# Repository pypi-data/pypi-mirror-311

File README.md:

# PyPI code 311

This repository is part of a project to make all code in PyPI as accessible as possible. For more information 
on the project and to find out how to utilise this data, see the website: https://py-code.org/

This repo contains 50000 packages uploaded to PyPI between 
2024-11-25 23:24 and 2024-11-29 07:17.

The repo is 99% (49999/50000) complete.

Package contents can be found [in the code branch](https://github.com/pypi-data/pypi-mirror-311/tree/code/packages).

A browsable package list for all repositories [all packages here](https://py-code.org/repositories/pypi-mirror-311).

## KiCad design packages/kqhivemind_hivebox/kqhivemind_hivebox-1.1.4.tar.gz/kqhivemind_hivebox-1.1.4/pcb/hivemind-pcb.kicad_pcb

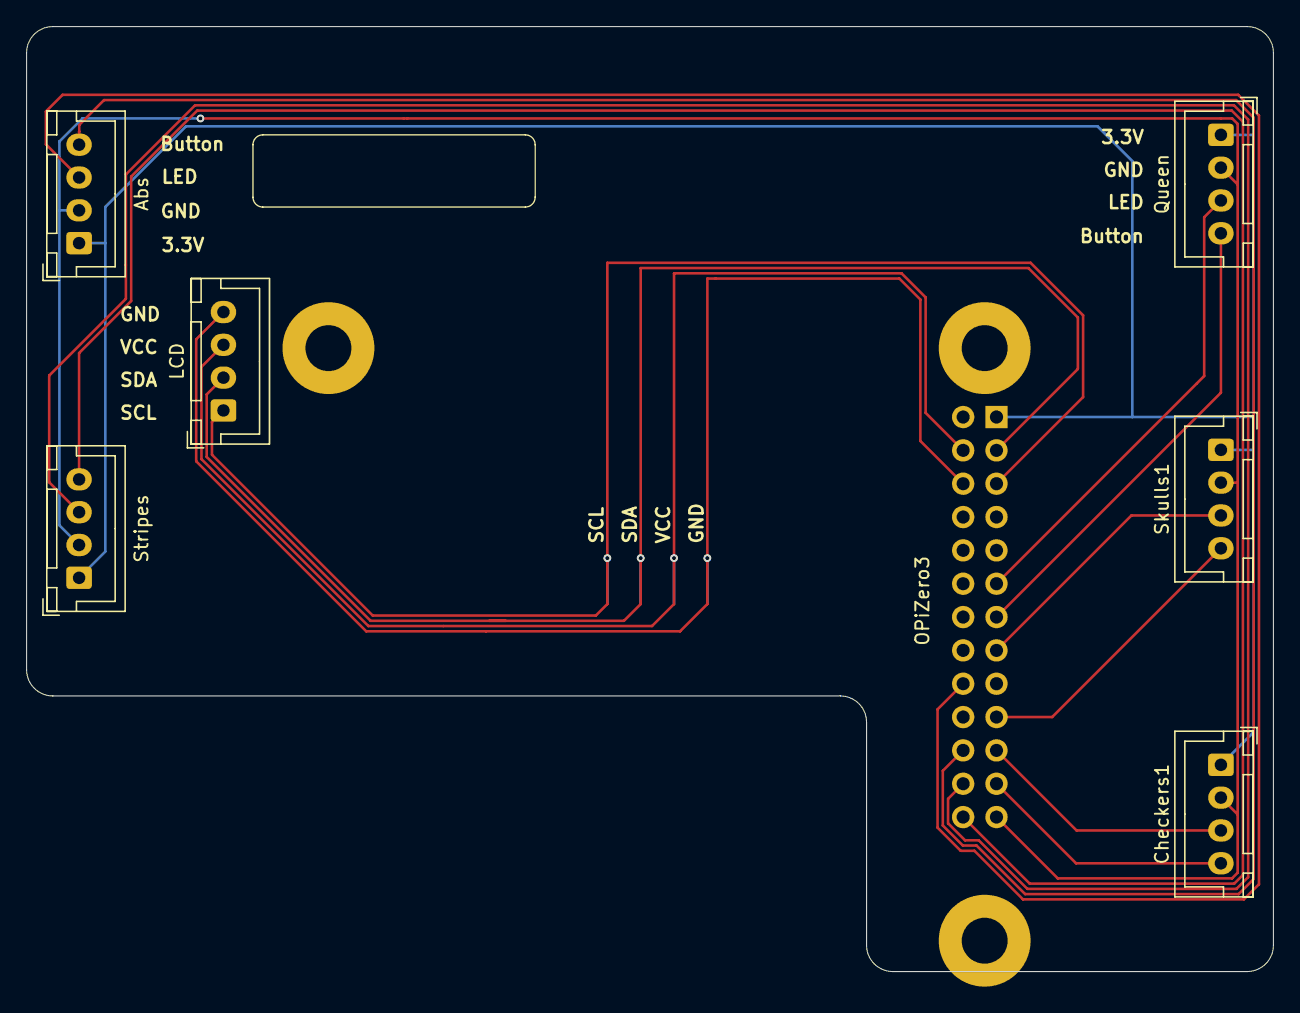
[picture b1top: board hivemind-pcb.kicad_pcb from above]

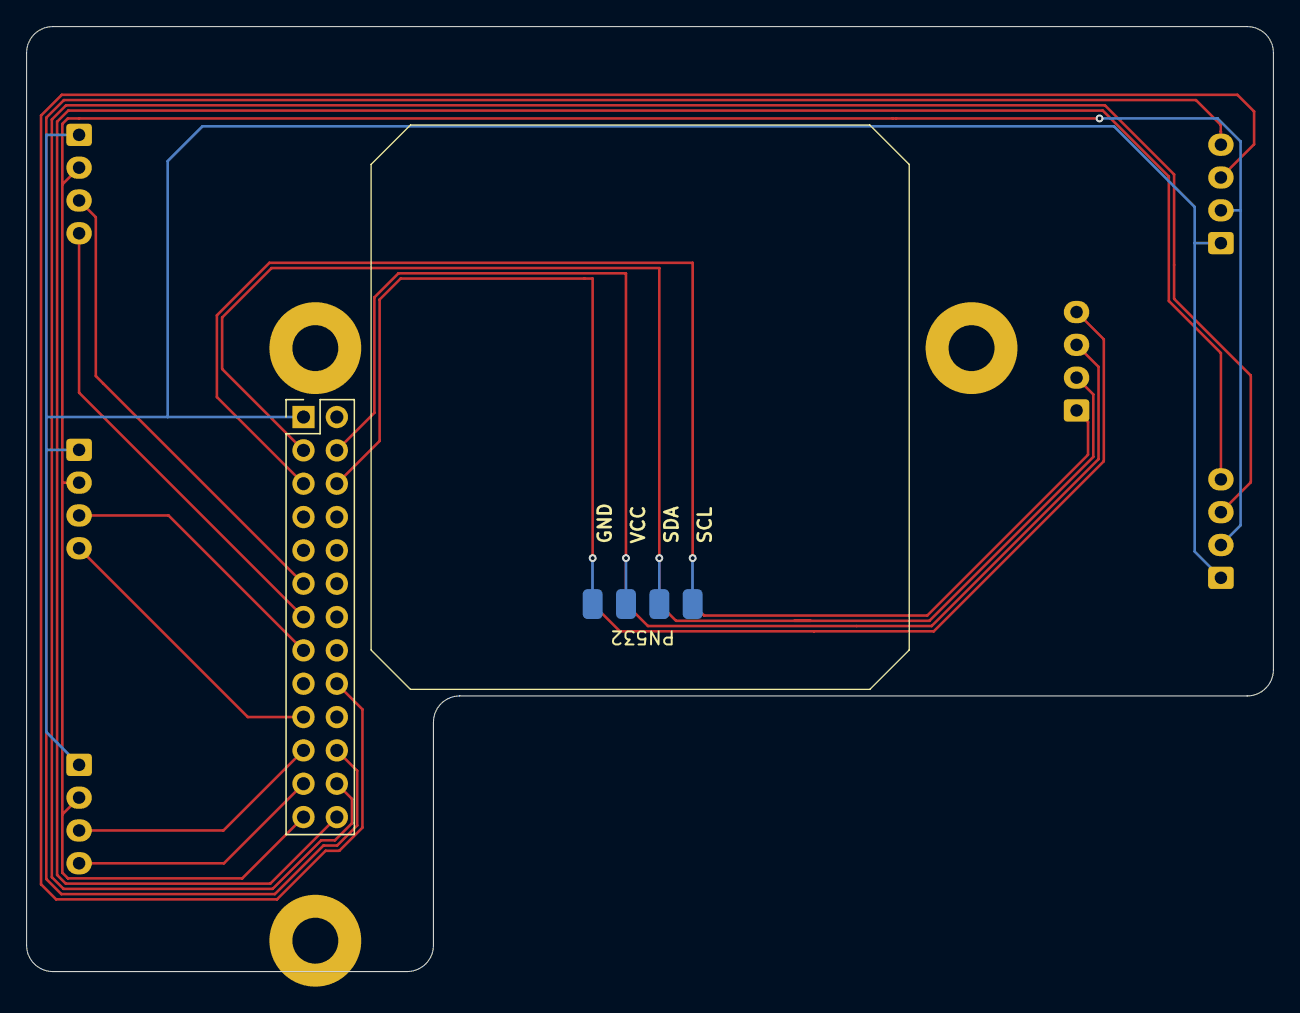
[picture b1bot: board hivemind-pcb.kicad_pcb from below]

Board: 2 copper layers, 95.0 x 72.0 mm, 8 parts (2 on the bottom side), 12 nets.

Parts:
Abs: Conn_01x04_Pin; JST_XH_B4B-XH-A_1x04_P2.50mm_Vertical
Checkers1: Conn_01x04_Pin; JST_XH_B4B-XH-A_1x04_P2.50mm_Vertical
LCD: Conn_01x04_Pin; JST_XH_B4B-XH-A_1x04_P2.50mm_Vertical
OPiZero3: Conn_02x13_Odd_Even; PinHeader_2x13_P2.54mm_Vertical
PN532: Conn_01x04_Pin; Solder Pads 01x04 2.54mm
Queen: Conn_01x04_Pin; JST_XH_B4B-XH-A_1x04_P2.50mm_Vertical
Skulls1: Conn_01x04_Pin; JST_XH_B4B-XH-A_1x04_P2.50mm_Vertical
Stripes: Conn_01x04_Pin; JST_XH_B4B-XH-A_1x04_P2.50mm_Vertical

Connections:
unnamed: Checkers1.1, OPiZero3.1 (3.3V), Queen.1, Skulls1.1, Stripes.1
unnamed: Checkers1.2, OPiZero3.25, Queen.2, Skulls1.2, Stripes.2
unnamed: LCD.4 (GND), OPiZero3.6, PN532.4 (GND)
unnamed: LCD.1 (SCK), OPiZero3.5 (SCK), PN532.1 (SCK)
unnamed: LCD.2 (SDA), OPiZero3.3 (SDA), PN532.2 (SDA)
unnamed: LCD.3 (VCC), OPiZero3.4, PN532.3 (VCC)
unnamed: OPiZero3.13 (PC5), Queen.4
unnamed: OPiZero3.11 (PC6), Queen.3
unnamed: OPiZero3.15 (PC8), Skulls1.3
unnamed: OPiZero3.19, Skulls1.4
unnamed: OPiZero3.24, Stripes.3
unnamed: OPiZero3.26, Stripes.4

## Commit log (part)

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2024-12-07 Add package xgcondb/743.641.349/xgcondb-743.641.349-cp310-cp310-win_amd64.whl
2024-12-07 Add package fake-bge-module/20241129/fake_bge_module-20241129-py3-none-any.whl
2024-12-07 Add package bsg-ide/2.0.1/bsg_ide-2.0.1-py3-none-any.whl
2024-12-07 Add package xgcondb/2832.76.37/xgcondb-2832.76.37-cp310-cp310-win_amd64.whl
2024-12-07 Add package xgcondb/734.164.978/xgcondb-734.164.978-cp37-cp37m-manylinux2014_x86_64.manylinux_2_17_x86_64.whl
2024-12-07 Add package xgcondb/2833.70.52/xgcondb-2833.70.52-cp37-cp37m-win_amd64.whl
2024-12-07 Add package xgcondb/5983.907.328/xgcondb-5983.907.328-cp311-cp311-win_amd64.whl
2024-12-07 Add package xgcondb/2843.58.11/xgcondb-2843.58.11-cp39-cp39-manylinux2014_aarch64.manylinux_2_17_aarch64.whl
2024-12-07 Add package xgcondb/734.414.150/xgcondb-734.414.150-cp37-cp37m-win_amd64.whl
2024-12-07 Add package xgcondb/2838.67.75/xgcondb-2838.67.75-cp39-cp39-manylinux2014_aarch64.manylinux_2_17_aarch64.whl
2024-12-07 Add package xgcondb/2833.70.52/xgcondb-2833.70.52-cp39-cp39-win_amd64.whl
2024-12-07 Add package xgcondb/5973.661.293/xgcondb-5973.661.293-cp310-cp310-win_amd64.whl
2024-12-07 Add package seatools/1.0.13/seatools-1.0.13-py3-none-any.whl
2024-12-07 Add package xgcondb/725.204.402/xgcondb-725.204.402-cp310-cp310-manylinux2014_x86_64.manylinux_2_17_x86_64.whl
2024-12-07 Add package streamlit-nightly/1.40.3.dev20241128/streamlit_nightly-1.40.3.dev20241128.tar.gz
2024-12-07 Add package xgcondb/5991.19.593/xgcondb-5991.19.593-cp37-cp37m-manylinux2014_x86_64.manylinux_2_17_x86_64.whl
2024-12-07 Add package xgcondb/5983.53.251/xgcondb-5983.53.251-cp37-cp37m-win_amd64.whl
2024-12-07 Add package xgcondb/2853.74.16/xgcondb-2853.74.16-cp39-cp39-manylinux2014_aarch64.manylinux_2_17_aarch64.whl
2024-12-07 Add package xgcondb/2853.66.40/xgcondb-2853.66.40-cp38-cp38-manylinux2014_x86_64.manylinux_2_17_x86_64.whl
2024-12-07 Add package xgcondb/735.844.684/xgcondb-735.844.684-cp311-cp311-win_amd64.whl
2024-12-07 Add package xgcondb/5992.370.685/xgcondb-5992.370.685-cp39-cp39-win_amd64.whl
2024-12-07 Add package xgcondb/5984.336.412/xgcondb-5984.336.412-cp311-cp311-win_amd64.whl
2024-12-07 Add package xgcondb/6008.274.512/xgcondb-6008.274.512-cp37-cp37m-win_amd64.whl
2024-12-07 Add package xgcondb/731.9.980/xgcondb-731.9.980-cp310-cp310-manylinux2014_x86_64.manylinux_2_17_x86_64.whl
2024-12-07 Add package xgcondb/725.7.854/xgcondb-725.7.854-cp310-cp310-manylinux2014_x86_64.manylinux_2_17_x86_64.whl
2024-12-07 Add package xgcondb/726.249.769/xgcondb-726.249.769-cp311-cp311-manylinux2014_x86_64.manylinux_2_17_x86_64.whl
2024-12-07 Add package xgcondb/2839.36.70/xgcondb-2839.36.70-cp38-cp38-manylinux2014_aarch64.manylinux_2_17_aarch64.whl
2024-12-07 Add package xgcondb/744.346.258/xgcondb-744.346.258-cp38-cp38-win_amd64.whl
2024-12-07 Add package xgcondb/5986.182.943/xgcondb-5986.182.943-cp38-cp38-win_amd64.whl
2024-12-07 Add package xgcondb/6009.5.900/xgcondb-6009.5.900-cp38-cp38-manylinux2014_x86_64.manylinux_2_17_x86_64.whl
2024-12-07 Add package xgcondb/2863.58.40/xgcondb-2863.58.40-cp37-cp37m-manylinux2014_aarch64.manylinux_2_17_aarch64.whl
2024-12-07 Add package xgcondb/2840.84.41/xgcondb-2840.84.41-cp38-cp38-manylinux2014_aarch64.manylinux_2_17_aarch64.whl
2024-12-07 Add package xgcondb/736.840.889/xgcondb-736.840.889-cp37-cp37m-win_amd64.whl
2024-12-07 Add package xgcondb/2855.65.91/xgcondb-2855.65.91-cp37-cp37m-manylinux2014_aarch64.manylinux_2_17_aarch64.whl
2024-12-07 Add package aliyun-python-sdk-bpstudio/1.0.13/aliyun_python_sdk_bpstudio-1.0.13-py2.py3-none-any.whl
2024-12-07 Add package xgcondb/751.653.359/xgcondb-751.653.359-cp37-cp37m-manylinux2014_aarch64.manylinux_2_17_aarch64.whl
2024-12-07 Add package xgcondb/5993.344.625/xgcondb-5993.344.625-cp39-cp39-win_amd64.whl
2024-12-07 Add package xgcondb/6008.204.105/xgcondb-6008.204.105-cp39-cp39-win_amd64.whl
2024-12-07 Add package xgcondb/740.701.827/xgcondb-740.701.827-cp39-cp39-manylinux2014_x86_64.manylinux_2_17_x86_64.whl
2024-12-07 Add package smart-steganography-lib/0.1.1/smart_steganography_lib-0.1.1-py3-none-any.whl
2024-12-07 Add package xgcondb/745.171.814/xgcondb-745.171.814-cp37-cp37m-manylinux2014_aarch64.manylinux_2_17_aarch64.whl
2024-12-07 Add package synth-sdk/0.2.80/synth_sdk-0.2.80-py3-none-any.whl
2024-12-07 Add package xgcondb/752.395.285/xgcondb-752.395.285-cp39-cp39-manylinux2014_aarch64.manylinux_2_17_aarch64.whl
2024-12-07 Add package EwanSonicConnector/0.1.7/ewansonicconnector-0.1.7.tar.gz
2024-12-07 Add package xgcondb/6010.245.110/xgcondb-6010.245.110-cp39-cp39-manylinux2014_aarch64.manylinux_2_17_aarch64.whl
2024-12-07 Add package xgcondb/2846.0.64/xgcondb-2846.0.64-cp39-cp39-win_amd64.whl
2024-12-07 Add package xgcondb/6010.481.789/xgcondb-6010.481.789-cp38-cp38-manylinux2014_aarch64.manylinux_2_17_aarch64.whl
2024-12-07 Add package mg-pso-gui/0.2.14/mg_pso_gui-0.2.14-py3-none-any.whl
2024-12-07 Add package xgcondb/5997.414.393/xgcondb-5997.414.393-cp37-cp37m-manylinux2014_x86_64.manylinux_2_17_x86_64.whl
2024-12-07 Add package ailia-llm/1.2.1.0/ailia_llm-1.2.1.0-py3-none-any.whl
2024-12-07 Add package xgcondb/5996.815.127/xgcondb-5996.815.127-cp39-cp39-manylinux2014_x86_64.manylinux_2_17_x86_64.whl
2024-12-07 Add package django-swifty/0.0.44/django_swifty-0.0.44.tar.gz
2024-12-07 Add package xgcondb/6000.465.492/xgcondb-6000.465.492-cp39-cp39-win_amd64.whl
2024-12-07 Add package xgcondb/753.969.148/xgcondb-753.969.148-cp37-cp37m-win_amd64.whl
2024-12-07 Add package xgcondb/737.258.167/xgcondb-737.258.167-cp37-cp37m-win_amd64.whl
2024-12-07 Add package xgcondb/6001.226.428/xgcondb-6001.226.428-cp310-cp310-manylinux2014_x86_64.manylinux_2_17_x86_64.whl
2024-12-07 Add package aiotica/1.0.12/aiotica-1.0.12-py3-none-any.whl
2024-12-07 Add package nemo-library/1.1.18/nemo_library-1.1.18.tar.gz
2024-12-07 Add package xgcondb/2847.62.7/xgcondb-2847.62.7-cp39-cp39-manylinux2014_x86_64.manylinux_2_17_x86_64.whl
2024-12-07 Add package rjj/0.8.9/rjj-0.8.9.tar.gz
2024-12-07 Add package xgcondb/746.75.683/xgcondb-746.75.683-cp39-cp39-manylinux2014_aarch64.manylinux_2_17_aarch64.whl
2024-12-07 Add package xgcondb/2865.72.17/xgcondb-2865.72.17-cp310-cp310-manylinux2014_x86_64.manylinux_2_17_x86_64.whl
2024-12-07 Add package xgcondb/740.246.716/xgcondb-740.246.716-cp37-cp37m-manylinux2014_x86_64.manylinux_2_17_x86_64.whl
2024-12-07 Add package xgcondb/6002.656.897/xgcondb-6002.656.897-cp310-cp310-win_amd64.whl
2024-12-07 Add package xgcondb/6026.1000.76/xgcondb-6026.1000.76-cp311-cp311-manylinux2014_x86_64.manylinux_2_17_x86_64.whl
2024-12-07 Add package aiotica/1.0.12/aiotica-1.0.12.tar.gz
2024-12-07 Add package xgcondb/754.523.504/xgcondb-754.523.504-cp37-cp37m-win_amd64.whl
2024-12-07 Add package xgcondb/6011.55.670/xgcondb-6011.55.670-cp311-cp311-manylinux2014_x86_64.manylinux_2_17_x86_64.whl
2024-12-07 Add package zope.app.wsgi/5.3/zope.app.wsgi-5.3-py3-none-any.whl
2024-12-07 Add package xgcondb/6012.36.609/xgcondb-6012.36.609-cp311-cp311-win_amd64.whl
2024-12-07 Add package xgcondb/2857.78.22/xgcondb-2857.78.22-cp39-cp39-manylinux2014_aarch64.manylinux_2_17_aarch64.whl
2024-12-07 Add package xgcondb/2866.96.13/xgcondb-2866.96.13-cp38-cp38-manylinux2014_x86_64.manylinux_2_17_x86_64.whl
2024-12-07 Add package xgcondb/739.371.181/xgcondb-739.371.181-cp310-cp310-win_amd64.whl
2024-12-07 Add package xgcondb/2866.74.29/xgcondb-2866.74.29-cp310-cp310-win_amd64.whl
2024-12-07 Add package xgcondb/755.456.312/xgcondb-755.456.312-cp39-cp39-manylinux2014_x86_64.manylinux_2_17_x86_64.whl
2024-12-07 Add package xursparks/1.1.2/xursparks-1.1.2-py3-none-any.whl
2024-12-07 Add package youqu-playbook/2024.11.29/youqu_playbook-2024.11.29-py3-none-any.whl
2024-12-07 Add package xgcondb/755.392.570/xgcondb-755.392.570-cp39-cp39-manylinux2014_x86_64.manylinux_2_17_x86_64.whl
2024-12-07 Add package xgcondb/6029.716.152/xgcondb-6029.716.152-cp37-cp37m-win_amd64.whl
2024-12-07 Add package xgcondb/742.103.16/xgcondb-742.103.16-cp311-cp311-manylinux2014_x86_64.manylinux_2_17_x86_64.whl
2024-12-07 Add package xgcondb/750.948.318/xgcondb-750.948.318-cp311-cp311-win_amd64.whl
2024-12-07 Add package xgcondb/749.107.109/xgcondb-749.107.109-cp37-cp37m-manylinux2014_aarch64.manylinux_2_17_aarch64.whl
2024-12-07 Add package xgcondb/2851.82.83/xgcondb-2851.82.83-cp310-cp310-manylinux2014_x86_64.manylinux_2_17_x86_64.whl
2024-12-07 Add package xgcondb/2868.53.12/xgcondb-2868.53.12-cp38-cp38-manylinux2014_aarch64.manylinux_2_17_aarch64.whl
2024-12-07 Add package xgcondb/756.160.564/xgcondb-756.160.564-cp39-cp39-manylinux2014_aarch64.manylinux_2_17_aarch64.whl
2024-12-07 Add package xgcondb/6029.631.377/xgcondb-6029.631.377-cp38-cp38-manylinux2014_x86_64.manylinux_2_17_x86_64.whl
2024-12-07 Add package InvoiceBuddy/0.3.1/invoicebuddy-0.3.1-py3-none-any.whl
2024-12-07 Add package mcsp/1.1.2/mcsp-1.1.2-py3-none-any.whl
2024-12-07 Add package remics/0.1.1/remics-0.1.1-py2.py3-none-any.whl
2024-12-07 Add package xgcondb/2858.58.67/xgcondb-2858.58.67-cp39-cp39-win_amd64.whl
2024-12-07 Add package xgcondb/751.331.865/xgcondb-751.331.865-cp37-cp37m-win_amd64.whl
2024-12-07 Add package xgcondb/2869.46.36/xgcondb-2869.46.36-cp39-cp39-manylinux2014_aarch64.manylinux_2_17_aarch64.whl
2024-12-07 Add package xgcondb/756.998.863/xgcondb-756.998.863-cp38-cp38-manylinux2014_x86_64.manylinux_2_17_x86_64.whl
2024-12-07 Add package xgcondb/749.650.587/xgcondb-749.650.587-cp311-cp311-manylinux2014_x86_64.manylinux_2_17_x86_64.whl
2024-12-07 Add package autonomize-sdk-python/0.0.0/autonomize_sdk_python-0.0.0-py3-none-any.whl
2024-12-07 Add package xgcondb/6018.471.398/xgcondb-6018.471.398-cp38-cp38-win_amd64.whl
2024-12-07 Add package xgcondb/6031.574.585/xgcondb-6031.574.585-cp39-cp39-manylinux2014_aarch64.manylinux_2_17_aarch64.whl
2024-12-07 Add package xgcondb/2858.85.71/xgcondb-2858.85.71-cp38-cp38-manylinux2014_x86_64.manylinux_2_17_x86_64.whl
2024-12-07 Add package xgcondb/748.97.298/xgcondb-748.97.298-cp38-cp38-manylinux2014_x86_64.manylinux_2_17_x86_64.whl
2024-12-07 Add package xgcondb/748.97.298/xgcondb-748.97.298-cp310-cp310-manylinux2014_x86_64.manylinux_2_17_x86_64.whl
2024-12-07 Add package alibabacloud-bpstudio20210931/6.0.3/alibabacloud_bpstudio20210931-6.0.3-py3-none-any.whl
2024-12-07 Add package xgcondb/2870.33.95/xgcondb-2870.33.95-cp38-cp38-manylinux2014_aarch64.manylinux_2_17_aarch64.whl
2024-12-07 Add package xgcondb/6016.407.462/xgcondb-6016.407.462-cp38-cp38-win_amd64.whl
2024-12-07 Add package xgcondb/6033.747.316/xgcondb-6033.747.316-cp310-cp310-win_amd64.whl
2024-12-07 Add package bsg-ide/2.2/bsg_ide-2.2-py3-none-any.whl
2024-12-07 Add package xgcondb/2871.29.55/xgcondb-2871.29.55-cp37-cp37m-manylinux2014_x86_64.manylinux_2_17_x86_64.whl
2024-12-07 Add package xgcondb/6038.460.532/xgcondb-6038.460.532-cp37-cp37m-win_amd64.whl
2024-12-07 Add package autonomize-sdk-python/0.0.3/autonomize_sdk_python-0.0.3.tar.gz
2024-12-07 Add package xgcondb/760.191.14/xgcondb-760.191.14-cp310-cp310-win_amd64.whl
2024-12-07 Add package xgcondb/760.191.14/xgcondb-760.191.14-cp311-cp311-win_amd64.whl
2024-12-07 Add package xgcondb/2871.29.55/xgcondb-2871.29.55-cp38-cp38-manylinux2014_x86_64.manylinux_2_17_x86_64.whl
2024-12-07 Add package xgcondb/759.290.539/xgcondb-759.290.539-cp311-cp311-manylinux2014_x86_64.manylinux_2_17_x86_64.whl
2024-12-07 Add package xgcondb/758.953.174/xgcondb-758.953.174-cp39-cp39-manylinux2014_x86_64.manylinux_2_17_x86_64.whl
2024-12-07 Add package spinsight/1.0.2/spinsight-1.0.2-py3-none-any.whl
2024-12-07 Add package xgcondb/2870.33.95/xgcondb-2870.33.95-cp39-cp39-manylinux2014_aarch64.manylinux_2_17_aarch64.whl
2024-12-07 Add package xgcondb/6035.832.201/xgcondb-6035.832.201-cp38-cp38-manylinux2014_aarch64.manylinux_2_17_aarch64.whl
2024-12-07 Add package vehicle-form-validator/1.0.0/vehicle_form_validator-1.0.0-py3-none-any.whl
2024-12-07 Add package jk_utils/0.2024.11.29/jk_utils-0.2024.11.29-py3-none-any.whl
2024-12-07 Add package xgcondb/757.401.616/xgcondb-757.401.616-cp311-cp311-manylinux2014_x86_64.manylinux_2_17_x86_64.whl
2024-12-07 Add package flatflow/0.0.7/flatflow-0.0.7-cp313-cp313-manylinux_2_28_x86_64.whl
2024-12-07 Add package xgcondb/2869.47.95/xgcondb-2869.47.95-cp38-cp38-manylinux2014_x86_64.manylinux_2_17_x86_64.whl
